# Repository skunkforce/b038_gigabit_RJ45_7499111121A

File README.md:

# edgy_board number b038
This design is part of the [edgy board project](https://github.com/skunkforce/edgy_boards).

# getting started
This repository uses submodules. After cloning use the command 

```$ git submodule update --init --recursive```

to pull the submodules before opening the project with kicad. 

# Tests
Tests can be found in [TESTS.md](TESTS.md)

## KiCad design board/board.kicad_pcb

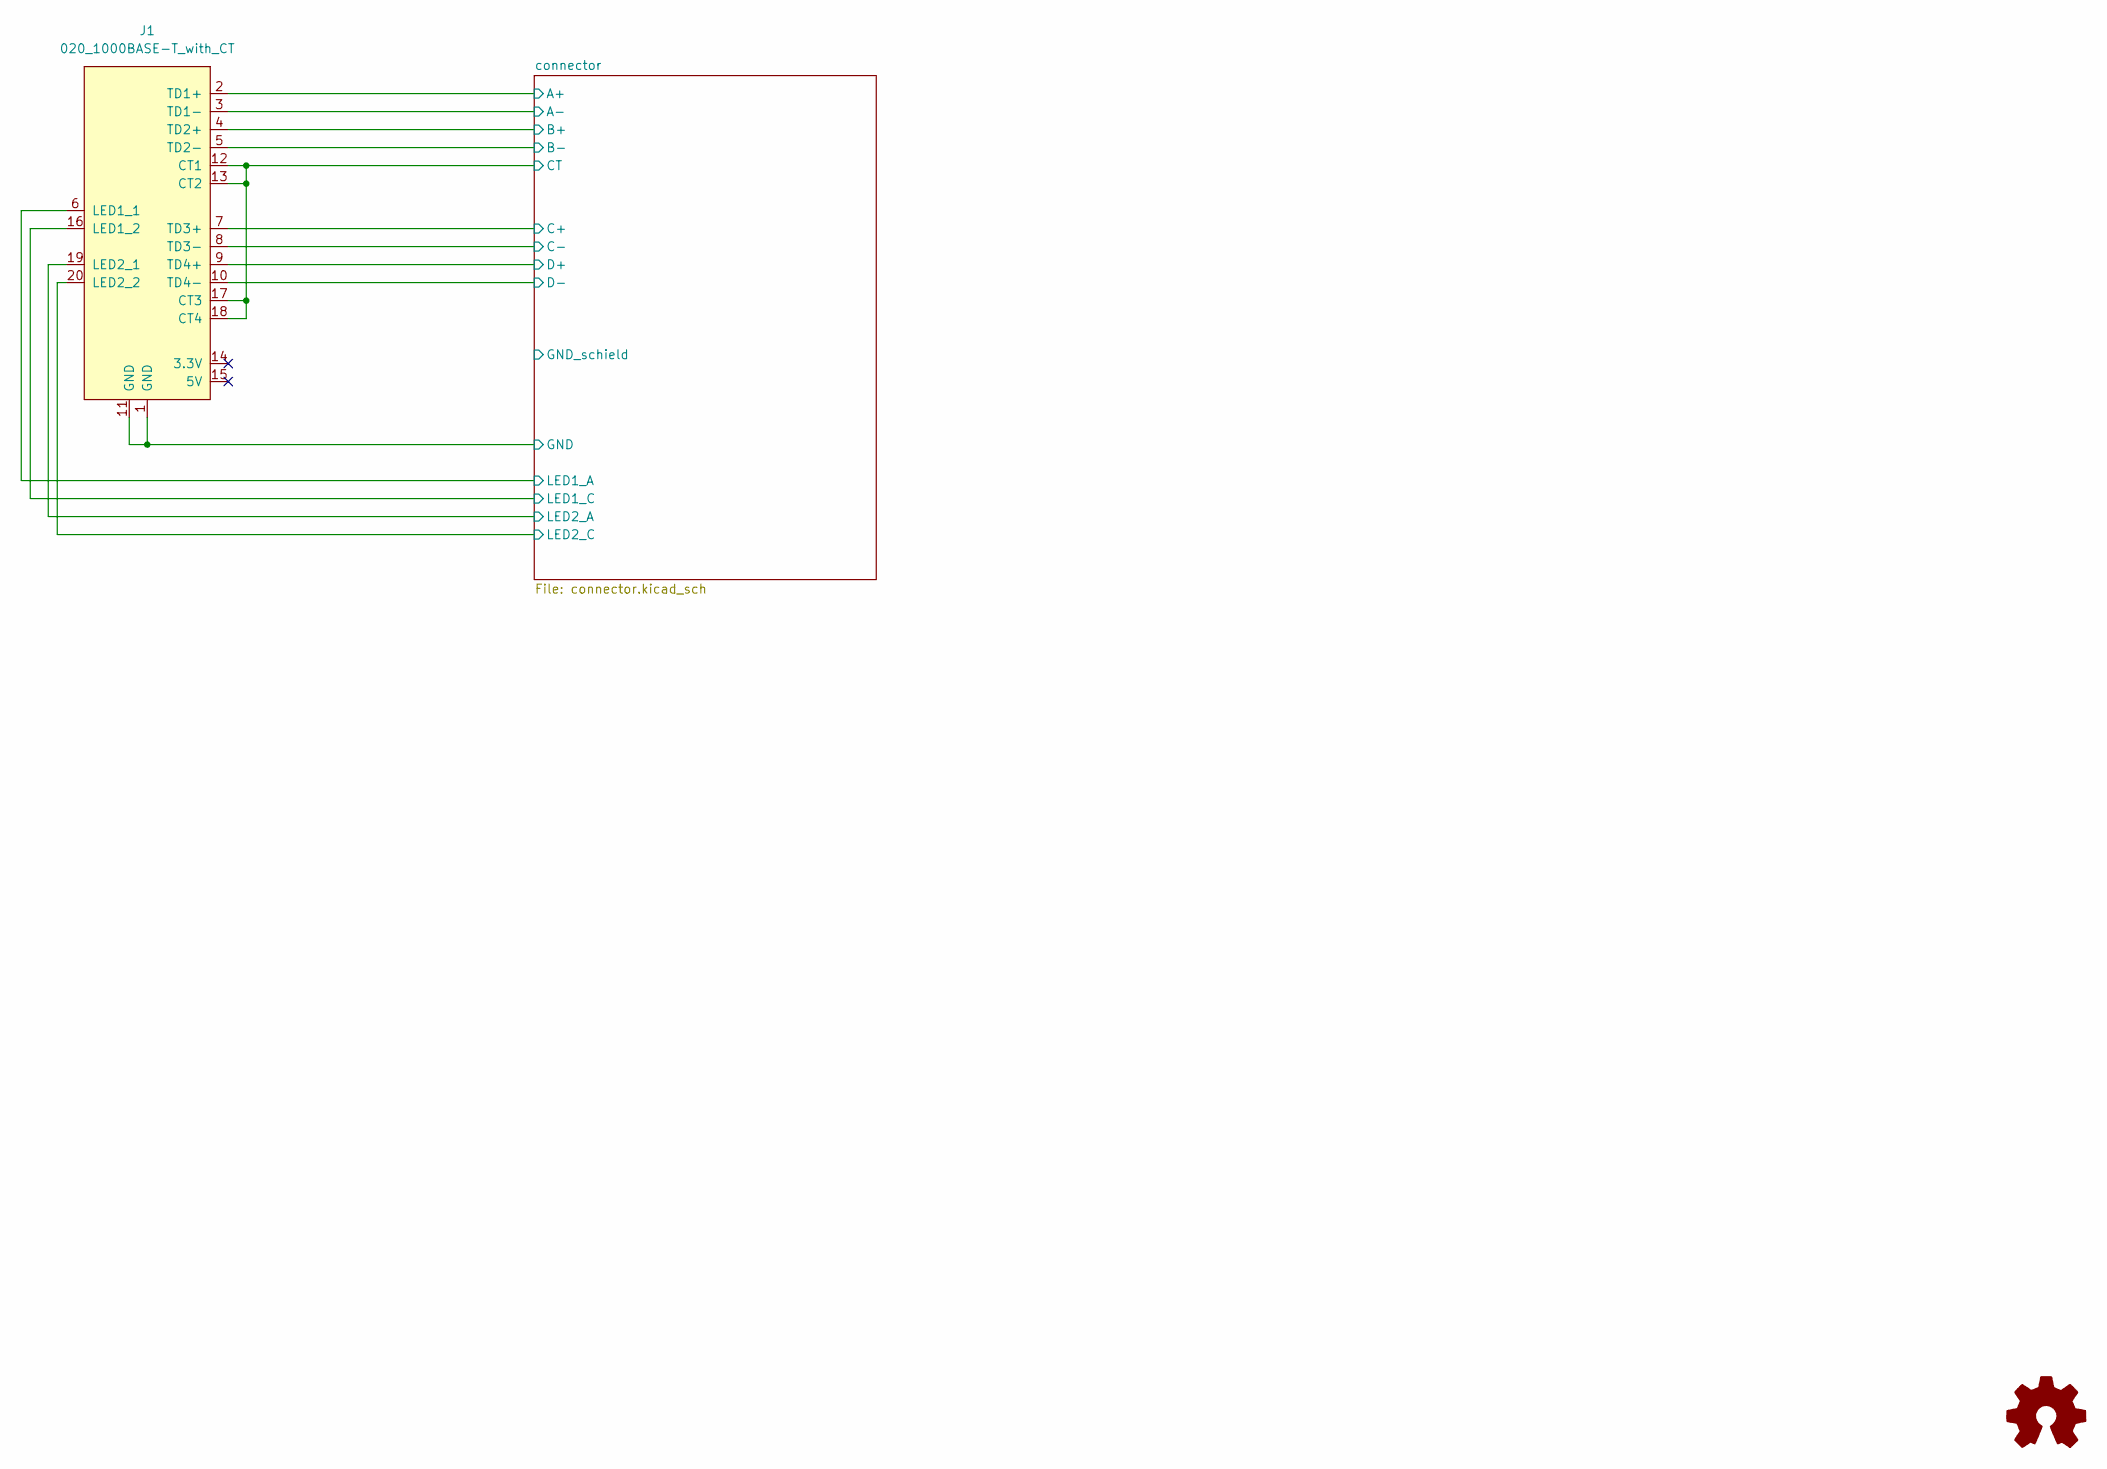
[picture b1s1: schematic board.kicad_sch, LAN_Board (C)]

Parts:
J1: 020_1000BASE-T_with_CT; on_edge_2x10_device
LOGO1: Logo_Open_Hardware_Small; OSHW-Symbol_6.7x6mm_SilkScreen

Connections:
/connector/A+: J1.2 (TD1+); also elsewhere on the board
/connector/A-: J1.3 (TD1-); also elsewhere on the board
/connector/B+: J1.4 (TD2+); also elsewhere on the board
/connector/B-: J1.5 (TD2-); also elsewhere on the board
/connector/C+: J1.7 (TD3+); also elsewhere on the board
/connector/C-: J1.8 (TD3-); also elsewhere on the board
/connector/CT: J1.12 (CT1), J1.13 (CT2), J1.17 (CT3), J1.18 (CT4); also elsewhere on the board
/connector/D+: J1.9 (TD4+); also elsewhere on the board
/connector/D-: J1.10 (TD4-); also elsewhere on the board
/connector/GND: J1.1 (GND), J1.11 (GND); also elsewhere on the board
/connector/LED1_A: J1.6 (LED1_1); also elsewhere on the board
/connector/LED1_C: J1.16 (LED1_2); also elsewhere on the board
/connector/LED2_A: J1.19 (LED2_1); also elsewhere on the board
/connector/LED2_C: J1.20 (LED2_2); also elsewhere on the board

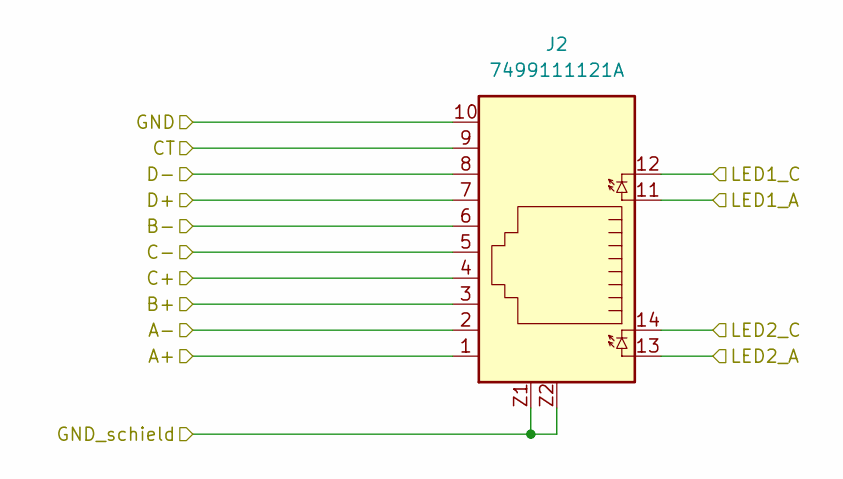
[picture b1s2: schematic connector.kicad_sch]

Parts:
J2: 7499111121A; MPN 7499111121A; Digi-Key_PN 1297-1070-5-ND

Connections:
/connector/A+: J2.1; also elsewhere on the board
/connector/A-: J2.2; also elsewhere on the board
/connector/B+: J2.3; also elsewhere on the board
/connector/B-: J2.6; also elsewhere on the board
/connector/C+: J2.4; also elsewhere on the board
/connector/C-: J2.5; also elsewhere on the board
/connector/CT: J2.9; also elsewhere on the board
/connector/D+: J2.7; also elsewhere on the board
/connector/D-: J2.8; also elsewhere on the board
/connector/GND: J2.10; also elsewhere on the board
/connector/GND_schield: J2.Z1, J2.Z2
/connector/LED1_A: J2.11; also elsewhere on the board
/connector/LED1_C: J2.12; also elsewhere on the board
/connector/LED2_A: J2.13; also elsewhere on the board
/connector/LED2_C: J2.14; also elsewhere on the board

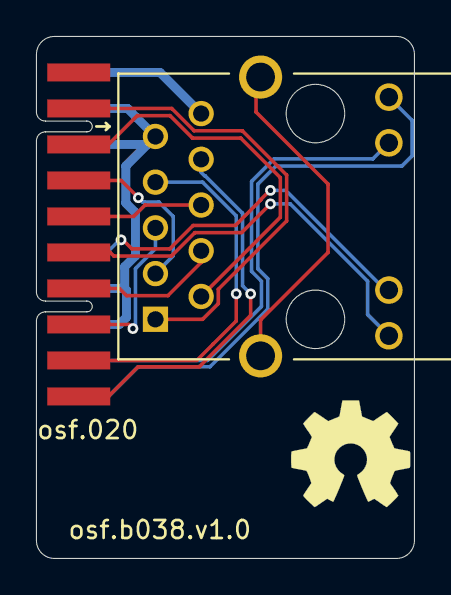
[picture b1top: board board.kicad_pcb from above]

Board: 4 copper layers, 21.0 x 29.0 mm, 3 parts (0 on the bottom side), 15 nets.

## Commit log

2023-03-08 initial
2023-03-08 generated 3d model
